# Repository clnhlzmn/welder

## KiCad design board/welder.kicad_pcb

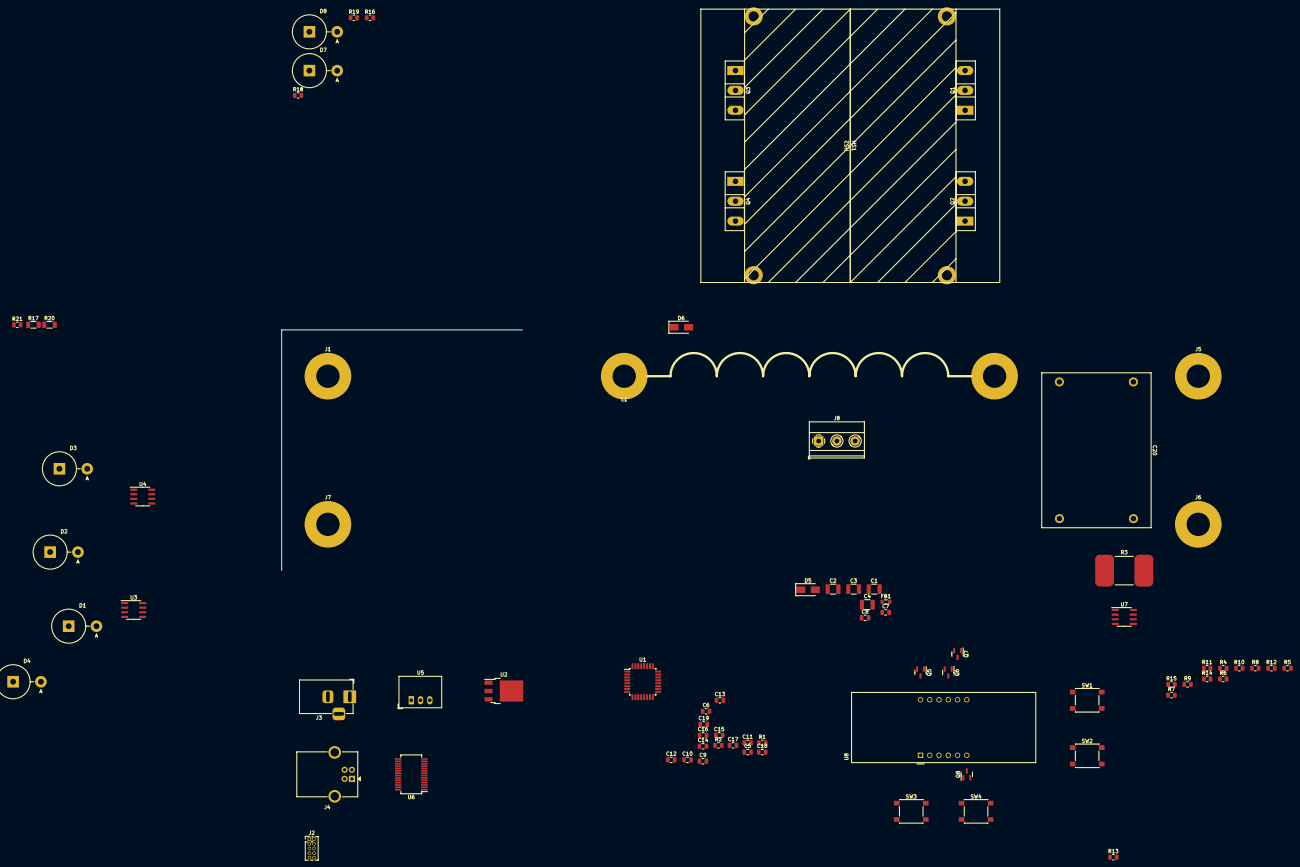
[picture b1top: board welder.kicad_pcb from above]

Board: 2 copper layers, 81 parts (0 on the bottom side), 70 nets, no tracks yet.

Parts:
C1, C2, C3, C4: 4.7 uF; C_1210_3225Metric
C5, C9: 10 uF; C_0805_2012Metric
C6, C7, C8, C10, C12, C13, C14, C15, C16, C19: 0.1 uF; C_0805_2012Metric
C11: 1 uF; C_0805_2012Metric
C17, C18: 47 pF; C_0805_2012Metric
C20: 50 uF; Cornell_Dublier_B10
D1, D2, D3, D4, D7, D8: 10A10-T; D_P600_R-6_P7.62mm_Vertical_AnodeUp
D5, D6: FML340A-W; D_SMA
FB1: FerriteBead; L_0805_2012Metric
HS1, HS2: Heatsink_Pad; Ohmite_C60-075
J1: VIN; MountingHole_6.4mm_M6_Pad
J2: Conn_01x10; PinHeader_2x05_P1.27mm_Vertical
J3: Barrel_Jack_Switch; BarrelJack_Horizontal
J4: USB_B; USB_B_OST_USB-B1HSxx_Horizontal
J5: POS; MountingHole_6.4mm_M6_Pad
J6: NEG; MountingHole_6.4mm_M6_Pad
J7: GND; MountingHole_6.4mm_M6_Pad
J8: EXT; TerminalBlock_Phoenix_MKDS-1,5-3_1x03_P5.00mm_Horizontal
L1: 20 uH; inductor
Q1, Q2, Q3, Q4: Q_NIGBT_GCE; TO-247-3_Vertical
Q5, Q6, Q7, Q8: Q_NPN_BEC; SOT-23
R1, R2: 100k; R_0805_2012Metric
R3: 0.0001; RES_5931
R4, R5, R6, R7, R8, R9, R10, R11: 220; R_0805_2012Metric
R12, R13, R14, R15: 470; R_0805_2012Metric
R16, R18, R19, R21: 0; R_0805_2012Metric
R17, R20: 3.3; R_1206_3216Metric
SW1: INC; SW_SPST_PTS645
SW2: DEC; SW_SPST_PTS645
SW3: SET; SW_SPST_PTS645
SW4: SEL; SW_SPST_PTS645
U1: ATSAMD21E18A-A; TQFP-32_7x7mm_P0.8mm
U2: LD1117ADT33TR; TO-252-3_TabPin2
U3, U4: MIC4604YM; SOIC-8_3.9x4.9mm_P1.27mm
U5: R-78E5.0-0.5; Converter_DCDC_RECOM_R-78E-0.5_THT
U6: FT232RL; SSOP-28_5.3x10.2mm_P0.65mm
U7: INA240A3D; SOIC-8_3.9x4.9mm_P1.27mm
U8: LTC-5723HR; CA56-12EWA

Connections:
/+3V3: C8.1, C9.1, C10.2, C15.1, C19.1, FB1.1, J2.1, J8.1, R1.1, R2.1, U1.30 (VDDIN), U2.3 (OUT), U6.4 (VCCIO), U7.3 (REF2), U7.6 (V+)
/+5V: C6.1, C13.1, C14.1, D5.1 (K), D6.2 (A), U2.1 (IN), U5.3 (OUT), U6.19 (~RESET), U6.20 (VCC)
/+15V: C1.2, C2.2, C12.1, D6.1 (K), J3.1, U3.1 (VDD), U4.1 (VDD), U5.1 (IN)
/+48V: D1.1 (K), D3.1 (K), J1.1, Q1.2 (C), Q3.2 (C)
/A: R4.1, U1.19 (PA18)
/AH: U1.5 (PA04), U3.5 (HI)
/AL: U1.15 (PA14), U3.6 (LI)
/B: R5.1, U1.20 (PA19)
/BH: U1.6 (PA05), U4.5 (HI)
/BL: U1.16 (PA15), U4.6 (LI)
/C: R6.1, U1.21 (PA22)
/D: R7.1, U1.22 (PA23)
/DEC: SW2.1, U1.2 (PA01)
/DIG1_EN: R12.2, U1.17 (PA16)
/DIG2_EN: R13.2, U1.18 (PA17)
/DIG3_EN: R14.2, U1.13 (PA10)
/DIG4_EN: R15.2, U1.14 (PA11)
/DP: R11.1, U1.27 (PA28)
/E: R8.1, U1.23 (PA24)
/EXT: J8.2, U1.8 (PA07)
/F: R9.1, U1.24 (PA25)
/G: R10.1, U1.25 (PA27)
/GND: C1.1, C2.1, C5.2, C6.2, C7.1, C8.2, C9.2, C10.1, C11.1, C12.2, C13.2, C14.2, C15.2, C16.2, C17.2, C18.2, C19.2, D2.2 (A), D4.2 (A), D7.2 (A), D8.2 (A), HS1.1, HS2.1, J2.3, J2.5, J3.2, J4.4 (GND), J4.5 (Shield), J7.1, J8.3, Q2.3 (E), Q4.3 (E), Q5.2 (E), Q6.2 (E), Q7.2 (E), Q8.2 (E), SW1.2, SW2.2, SW3.2, SW4.2, U1.10 (GND), U1.28 (GND), U2.2 (GND), U3.7 (VSS), U4.7 (VSS), U5.2 (GND), U6.7 (GND), U6.18 (GND), U6.21 (GND), U6.25 (AGND), U6.26 (TEST), U7.2 (GND), U7.4 (GND), U7.7 (REF1)
/INC: SW1.1, U1.1 (PA00)
/RX: U1.12 (PA09), U6.1 (TXD)
/SEL: SW4.1, U1.7 (PA06)
/SENSE: U1.3 (PA02), U7.5
/SENSE+: C20.2, J6.1, R3.2, U7.8 (+)
/SENSE-: D3.2 (A), D4.1 (K), Q3.3 (E), Q4.2 (C), R3.1, R20.2, U7.1 (-)
/SET: SW3.1, U1.4 (PA03)
/SWCLK: J2.4, R1.2, U1.31 (PA30)
/SWDIO: J2.2, U1.32 (PA31)
/TX: U1.11 (PA08), U6.5 (RXD)
/nRESET: J2.10, R2.2, U1.26 (~RESET)
unnamed: C3.1, D7.1 (K), R17.1, U3.4 (HS)
unnamed: C3.2, U3.2 (HB)
unnamed: C4.1, D8.1 (K), R20.1, U4.4 (HS)
unnamed: C4.2, U4.2 (HB)
unnamed: C5.1, C7.2, FB1.2, U1.9 (VDDANA)
unnamed: C11.2, U1.29 (VDDCORE)
unnamed: C16.1, U6.17 (3V3OUT)
unnamed: C17.1, J4.2 (D-), U6.16 (USBD-)
unnamed: C18.1, J4.3 (D+), U6.15 (USBD+)
unnamed: C20.1, J5.1, L1.2
unnamed: D1.2 (A), D2.1 (K), L1.1, Q1.3 (E), Q2.2 (C), R17.2
unnamed: D5.2 (A), J4.1 (VBUS)
unnamed: Q1.1 (G), R16.2
unnamed: Q2.1 (G), R18.2
unnamed: Q3.1 (G), R19.2
unnamed: Q4.1 (G), R21.2
unnamed: Q5.1 (B), R12.1
unnamed: Q5.3 (C), U8.12 (CC1)
unnamed: Q6.1 (B), R13.1
unnamed: Q6.3 (C), U8.9 (CC2)
unnamed: Q7.1 (B), R14.1
unnamed: Q7.3 (C), U8.8 (CC3)
unnamed: Q8.1 (B), R15.1
unnamed: Q8.3 (C), U8.6 (CC4)
unnamed: R4.2, U8.11 (a)
unnamed: R5.2, U8.7 (b)
unnamed: R6.2, U8.4 (c)
unnamed: R7.2, U8.2 (d)
unnamed: R8.2, U8.1 (e)
unnamed: R9.2, U8.10 (f)
unnamed: R10.2, U8.5 (g)
unnamed: R11.2, U8.3 (DPX)
unnamed: R16.1, U3.3 (HO)
unnamed: R18.1, U3.8 (LO)
unnamed: R19.1, U4.3 (HO)
unnamed: R21.1, U4.8 (LO)

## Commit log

2021-12-31 added igbts and drivers
2021-12-31 updated power supplies
2021-12-31 added filter simulation
2021-12-31 updated filter simulation
2022-01-01 added igbt.asc
2022-01-01 update igbt models with better parts
2022-01-01 added diy igbt model to filter sim
2022-01-01 remove NIGBT from filter sim
2022-01-03 filter sim
2022-01-09 Add fw diodes
2022-01-10 Added a bunch of stuff to schematic
2022-01-10 Add pwm, pol truth table
2022-01-10 Removed logic chips, it can be done in the SAM
2022-01-10 Moved *H and *L signals to complementary outputs for DTI
2022-01-10 Annotated schematic
2022-01-11 Updated PNs and footprints
2022-01-11 Add Cornell Dublier B10 footprint
2022-01-12 Added big resistor and inductor footprints and updated board
2022-01-13 added display, fixed up field names, updated board
2022-01-14 Add buttons, update board
2022-01-16 Added Rg and HS protection
2022-01-16 Added bom(s)
2022-01-16 add heatsinks
